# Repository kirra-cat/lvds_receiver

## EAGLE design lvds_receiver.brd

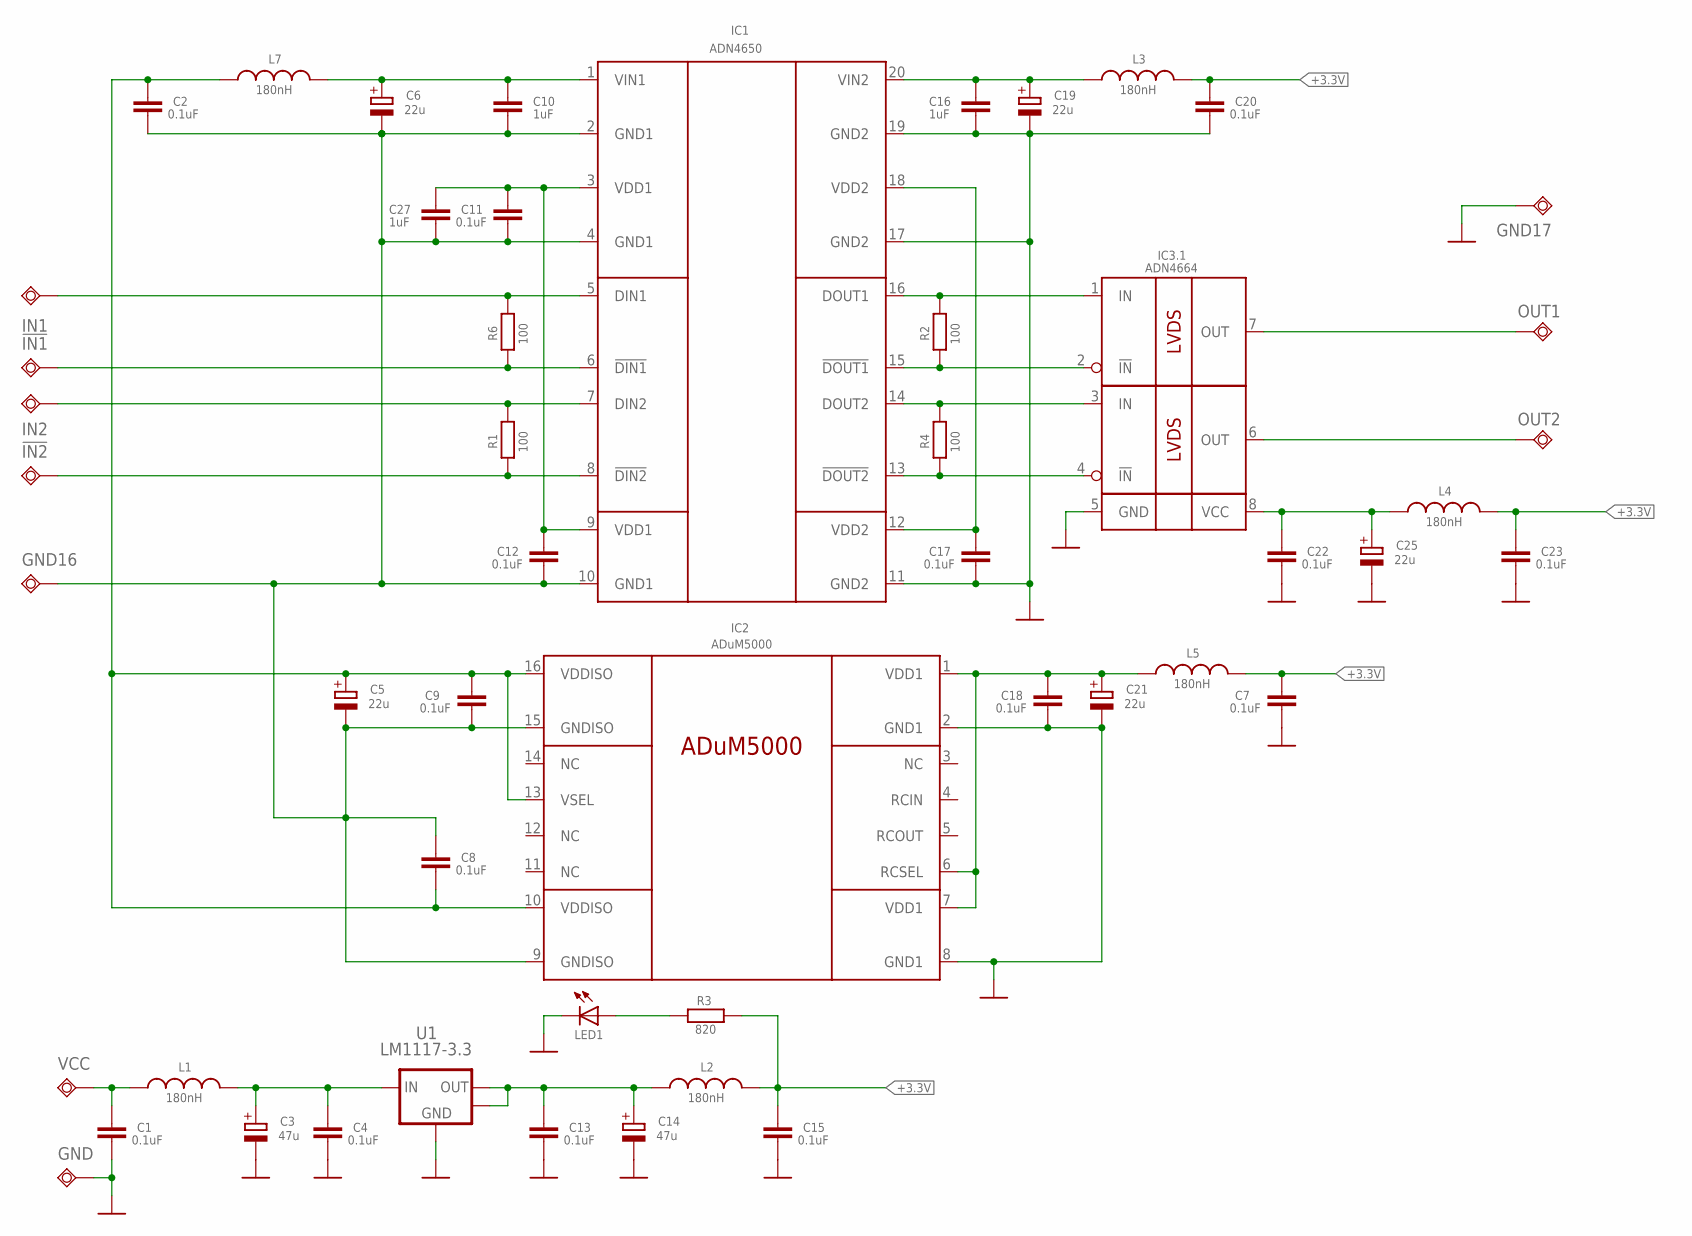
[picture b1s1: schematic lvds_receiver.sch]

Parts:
!IN1, !IN2: TPSQTP20R; TP20R
C1, C2, C4, C7, C8, C9, C11, C12, C13, C15, C17, C18, C20, C22, C23: 0.1uF; SMD0603
C3, C14: 47u; SMC_C
C5, C6, C19, C21, C25: 22u; SMC_A
C10, C16, C27: 1uF; SMD0603
GND, GND16, GND17: TPSQTP20R; TP20R
IC1: ADN4650; SO20W
IC2: ADuM5000; SO16W
IC3: ADN4664; SO08
IN1, IN2: TPSQTP20R; TP20R
L1, L2, L3, L4, L5, L7: 180nH; SMD0603
LED1: LEDCHIPLED_0805; CHIPLED_0805
OUT1, OUT2: TPSQTP20R; TP20R
R1, R2, R4, R6: 100; SMD0603
R3: 820; SMD0603
U1: LM1117-3.3; SOT223
VCC: TPSQTP20R; TP20R

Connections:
+3.3V: C7.1, C15.1, C20.1, C23.1, L2.2, L3.2, L4.2, L5.2, R3.2
GND: C1.2, C3.-, C4.2, C7.2, C13.2, C14.-, C15.2, C16.2, C17.2, C18.2, C19.-, C20.2, C21.-, C22.2, C23.2, C25.-, GND.TP, GND17.TP, IC1.11 (GND2), IC1.17 (GND2), IC1.19 (GND2), IC2.2 (GND1), IC2.8 (GND1), IC3.5 (GND), LED1.C, U1.1 (GND)
GND1: C2.2, C5.-, C6.-, C8.1, C9.2, C10.2, C11.2, C12.2, C27.2, GND16.TP, IC1.2 (GND1), IC1.4 (GND1), IC1.10 (GND1), IC2.9 (GNDISO), IC2.15 (GNDISO)
unnamed: IC1.5 (DIN1), IN1.TP, R6.2
unnamed: !IN1.TP, IC1.6 (!DIN1), R6.1
unnamed: IC1.7 (DIN2), IN2.TP, R1.2
unnamed: !IN2.TP, IC1.8 (!DIN2), R1.1
unnamed: IC3.7 (OUT), OUT1.TP
unnamed: C11.1, C12.1, C27.1, IC1.3 (VDD1), IC1.9 (VDD1)
unnamed: IC1.16 (DOUT1), IC3.1 (IN), R2.2
unnamed: IC1.14 (DOUT2), IC3.3 (IN), R4.2
unnamed: IC1.15 (!DOUT1), IC3.2 (!IN), R2.1
unnamed: IC1.13 (!DOUT2), IC3.4 (!IN), R4.1
unnamed: C2.1, C5.+, C8.2, C9.1, IC2.10 (VDDISO), IC2.13 (VSEL), IC2.16 (VDDISO), L7.1
unnamed: C6.+, C10.1, IC1.1 (VIN1), L7.2
unnamed: C3.+, C4.1, L1.2, U1.3 (IN)
unnamed: C22.1, C25.+, IC3.8 (VCC), L4.1
unnamed: C16.1, C19.+, IC1.20 (VIN2), L3.1
unnamed: C17.1, IC1.12 (VDD2), IC1.18 (VDD2)
unnamed: IC3.6 (OUT), OUT2.TP
unnamed: C1.1, L1.1, VCC.TP
unnamed: LED1.A, R3.1
NET000: C18.1, C21.+, IC2.1 (VDD1), IC2.6 (RCSEL), IC2.7 (VDD1), L5.1
OUT: C13.1, C14.+, L2.1, U1.2 (OUT), U1.4 (MASS)

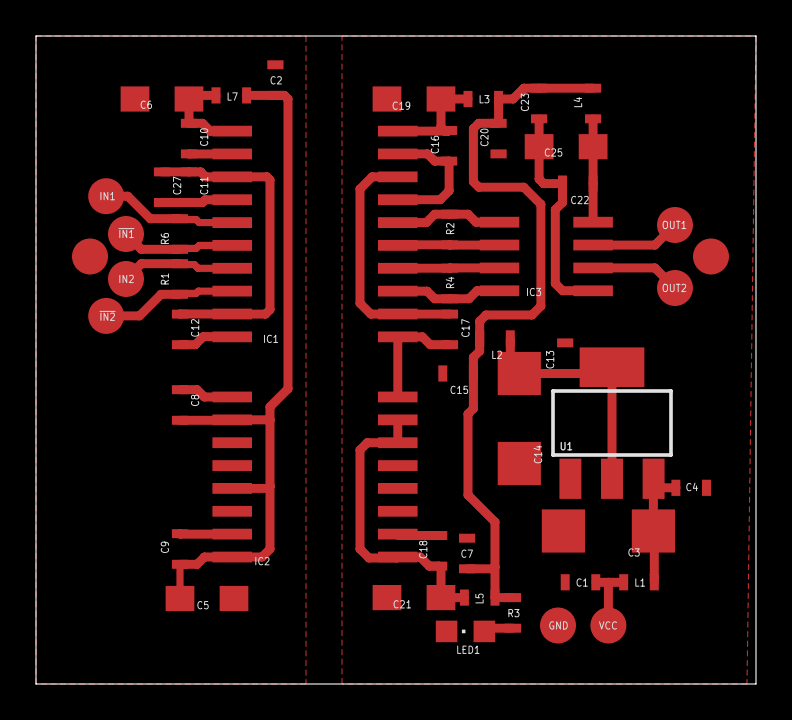
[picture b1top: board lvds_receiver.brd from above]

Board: 2 copper layers, 40.0 x 36.0 mm, 51 parts (0 on the bottom side), 24 nets.

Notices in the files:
parts and their libraries:
vreg-linear: 2009 Draw by Ivan A-R. License CC-BY-SA 3.0
